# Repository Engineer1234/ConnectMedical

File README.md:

# Connect-Med-Hardware
Repository for Hardware files relating to Connect Medical

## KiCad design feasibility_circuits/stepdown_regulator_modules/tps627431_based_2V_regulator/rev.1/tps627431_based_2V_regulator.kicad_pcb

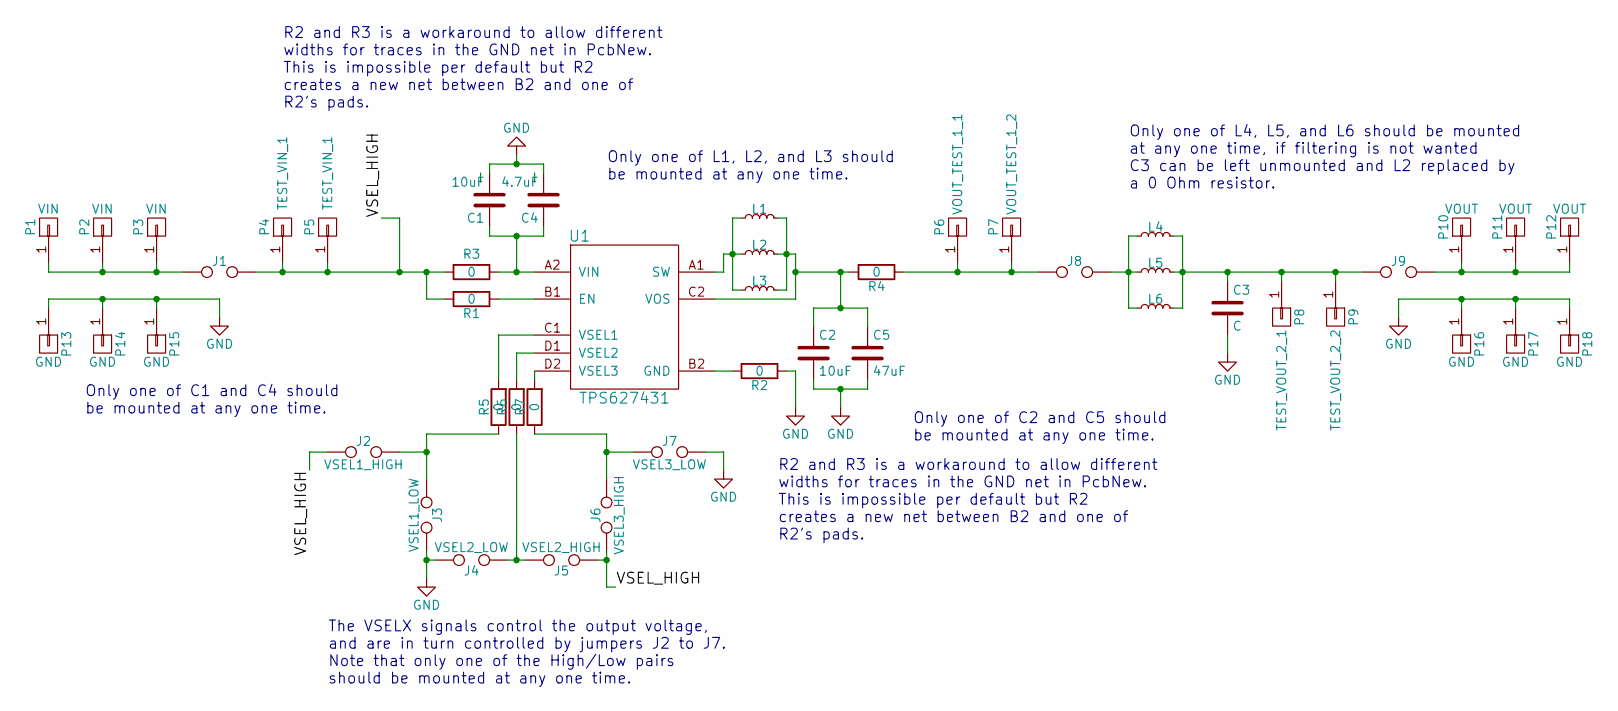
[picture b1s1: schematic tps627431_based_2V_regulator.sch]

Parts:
C1, C2: 10uF; C_0805_HandSoldering
C3: C; C_0805_HandSoldering
C4: 4.7uF; C_0402
C5: 47uF; C_0805_HandSoldering
J1, J8, J9: TEST; proto_header-vt-1x2-2.54mm-G_C__SABN_M30
J2: VSEL1_HIGH; proto_header-vt-1x2-2.54mm-G_C__SABN_M30
J3: VSEL1_LOW; proto_header-vt-1x2-2.54mm-G_C__SABN_M30
J4: VSEL2_LOW; proto_header-vt-1x2-2.54mm-G_C__SABN_M30
J5: VSEL2_HIGH; proto_header-vt-1x2-2.54mm-G_C__SABN_M30
J6: VSEL3_HIGH; proto_header-vt-1x2-2.54mm-G_C__SABN_M30
J7: VSEL3_LOW; proto_header-vt-1x2-2.54mm-G_C__SABN_M30
L1: L_Small; proto_inductor-WE_74404043100A_455x360
L2, L6: L_Small; proto_inductor-smd_1210
L3: L_Small; proto_inductor-WE_74404064220_640x570
L4: L_Small; proto_inductor-smd_1008
L5: L_Small; proto_inductor-smd_0805
P1, P2, P3: VIN; proto_pad-square-3mm
P4, P5: TEST_VIN_1; proto_pad-square-3mm
P6: VOUT_TEST_1_1; proto_pad-square-3mm
P7: VOUT_TEST_1_2; proto_pad-square-3mm
P8: TEST_VOUT_2_1; proto_pad-square-3mm
P9: TEST_VOUT_2_2; proto_pad-square-3mm
P10, P11, P12: VOUT; proto_pad-square-3mm
P13, P14, P15, P16, P17, P18: GND; proto_pad-square-3mm
R1, R2, R3, R4, R5, R6, R7: 0; R_0805_HandSoldering
U1: TPS627431; proto_amp-ti_tps624731

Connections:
/VSEL_HIGH: J1.2, J2.1, J5.1, J6.1, P4.1, P5.1, R1.2, R3.2
GND: C1.2, C2.2, C3.2, C4.2, C5.2, J3.2, J4.2, J7.2, P13.1, P14.1, P15.1, P16.1, P17.1, P18.1, R2.1
unnamed: C1.1, C4.1, R3.1, U1.A2 (VIN)
unnamed: C2.1, C5.1, L1.2, L2.2, L3.2, R4.2, U1.C2 (VOS)
unnamed: C3.1, J9.1, L4.2, L5.2, L6.2, P8.1, P9.1
unnamed: J1.1, P1.1, P2.1, P3.1
unnamed: J2.2, J3.1, R5.1
unnamed: J4.1, J5.2, R6.1
unnamed: J6.2, J7.1, R7.1
unnamed: J8.1, P6.1, P7.1, R4.1
unnamed: J8.2, L4.1, L5.1, L6.1
unnamed: J9.2, P10.1, P11.1, P12.1
unnamed: L1.1, L2.1, L3.1, U1.A1 (SW)
unnamed: R1.1, U1.B1 (EN)
unnamed: R2.2, U1.B2 (GND)
unnamed: R5.2, U1.C1 (VSEL1)
unnamed: R6.2, U1.D1 (VSEL2)
unnamed: R7.2, U1.D2 (VSEL3)

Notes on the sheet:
Only one of L4, L5, and L6 should be mounted at any one time, if filtering is not wanted C3 can be left unmounted and L2 replaced by a 0 Ohm resistor.
Only one of L1, L2, and L3 should be mounted at any one time.
The VSELX signals control the output voltage, and are in turn controlled by jumpers J2 to J7. Note that only one of the High/Low pairs should be mounted at any one time.
Only one of C1 and C4 should be mounted at any one time.
Only one of C2 and C5 should be mounted at any one time.
R2 and R3 is a workaround to allow different widths for traces in the GND net in PcbNew. This is impossible per default but R2 creates a new net between B2 and one of R2's pads.

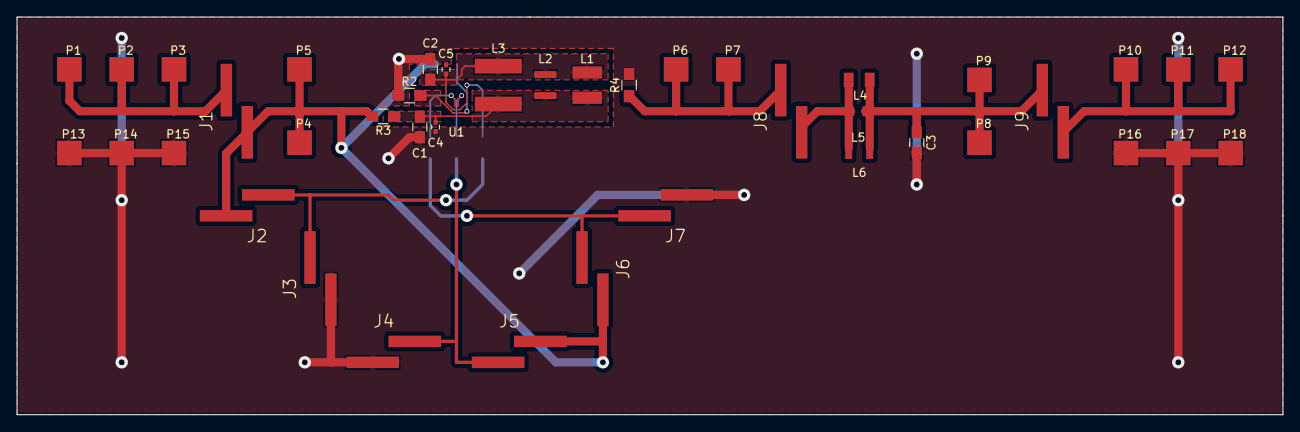
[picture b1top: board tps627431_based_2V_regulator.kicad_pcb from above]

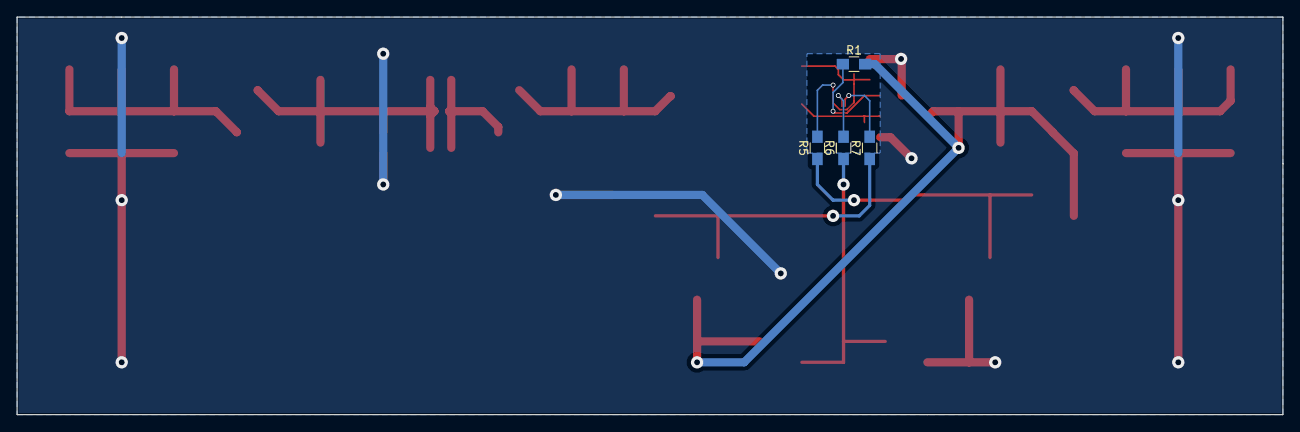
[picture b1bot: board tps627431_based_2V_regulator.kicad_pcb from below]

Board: 2 copper layers, 153.7 x 48.3 mm, 46 parts (4 on the bottom side), 18 nets.

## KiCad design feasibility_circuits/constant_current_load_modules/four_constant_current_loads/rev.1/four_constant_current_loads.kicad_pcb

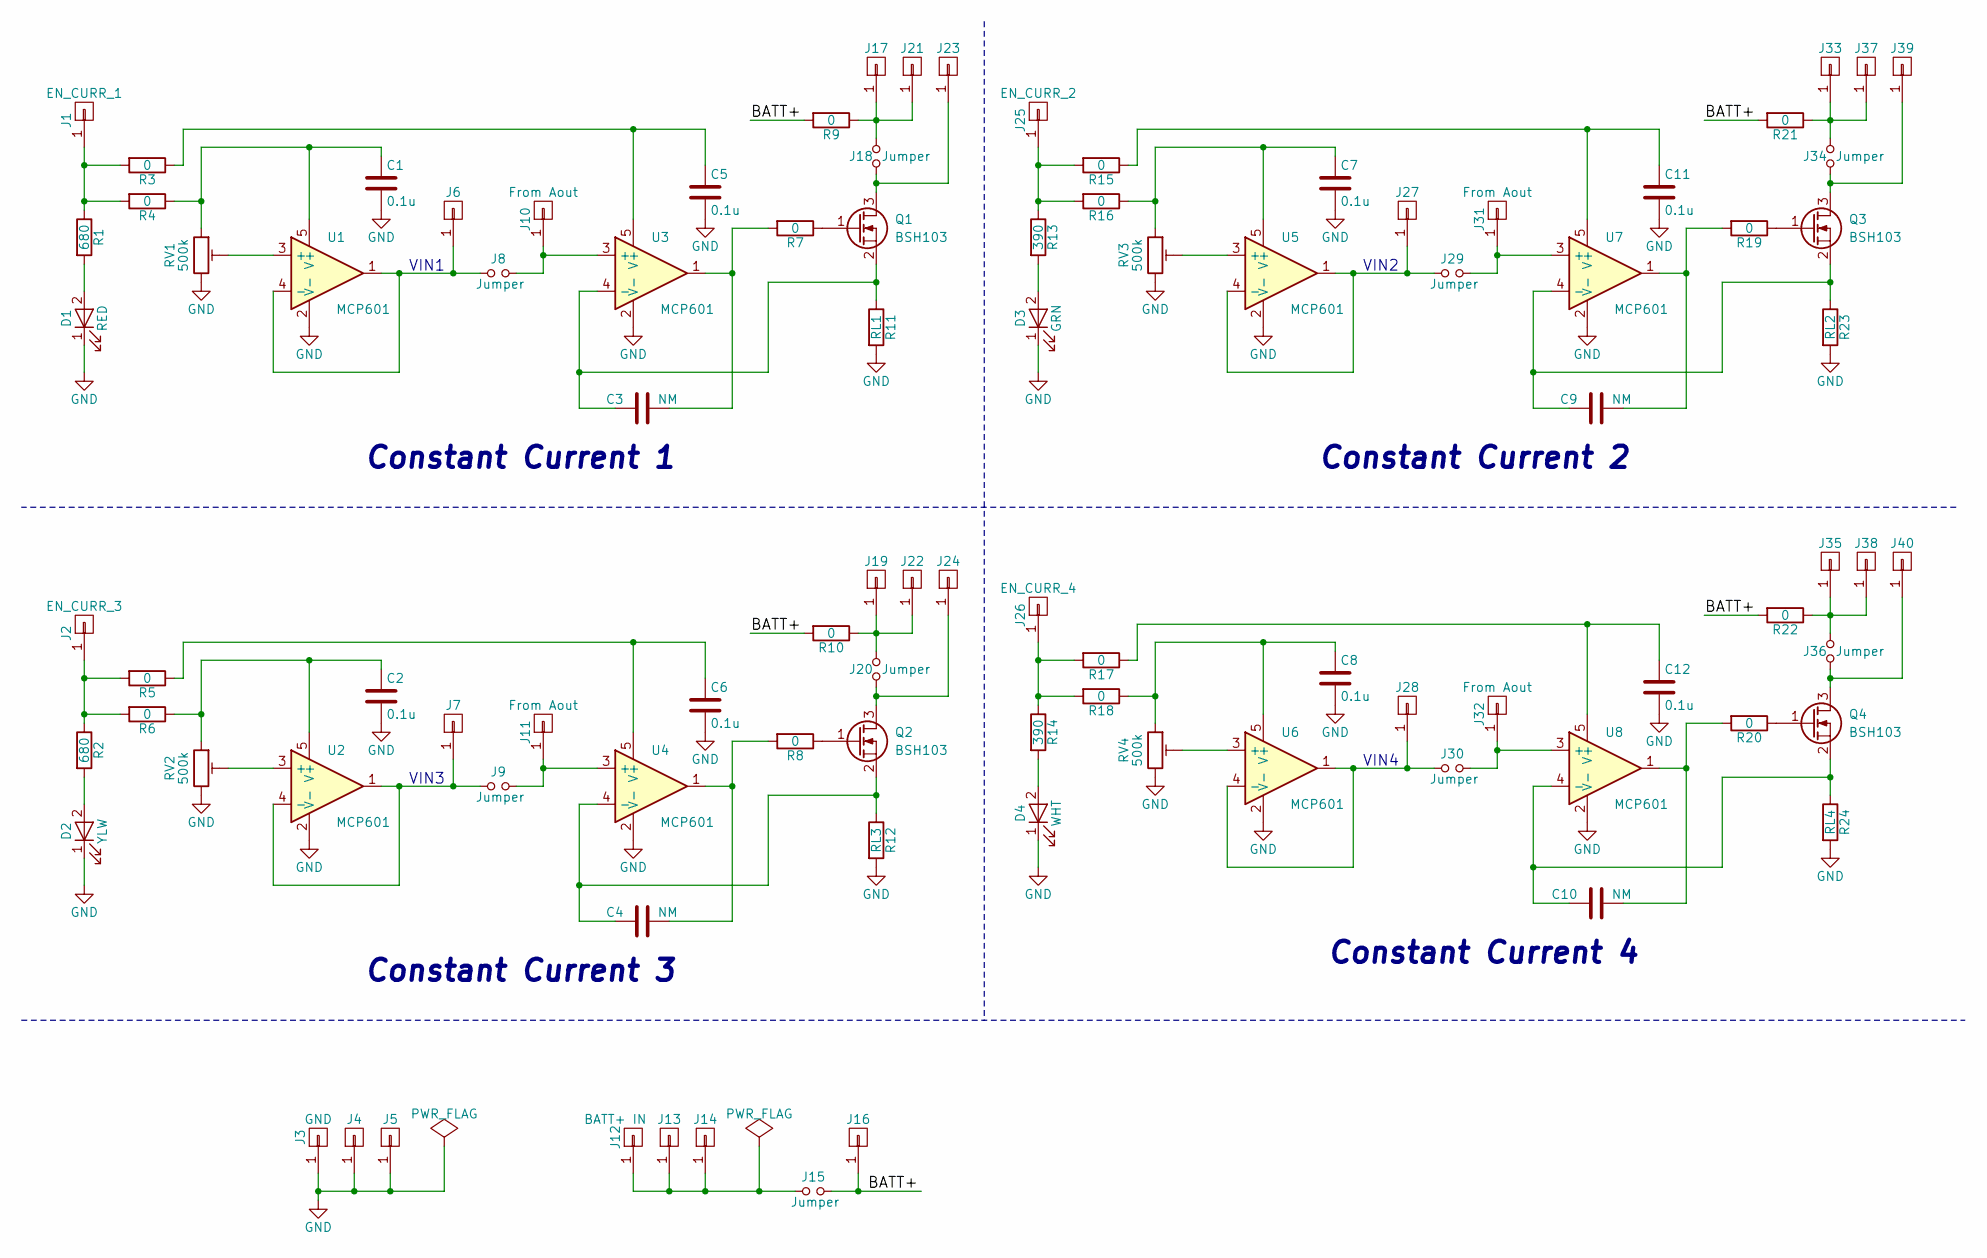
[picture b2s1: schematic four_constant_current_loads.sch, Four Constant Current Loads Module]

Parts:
C1, C2, C5, C6, C7, C8, C11, C12: 0.1u; C_0805_HandSoldering
C3, C4, C9, C10: NM; C_0805_HandSoldering
D1: RED; R_0805_HandSoldering
D2: YLW; R_0805_HandSoldering
D3: GRN; R_0805_HandSoldering
D4: WHT; R_0805_HandSoldering
J1: EN_CURR_1; proto_pad-square-3mm
J2: EN_CURR_3; proto_pad-square-3mm
J3, J4, J5, J6, J7, J13, J14, J16, J17, J19, J21, J22, J23, J24, J27, J28, J33, J35, J37, J38, J39, J40: GND; proto_pad-square-3mm
J8, J9, J15, J18, J20, J29, J30, J34, J36: Jumper; proto_header-vt-1x2-2.54mm-G_C__SABN_M30
J10, J11, J31, J32: From Aout; proto_pad-square-3mm
J12: BATT+ IN; proto_pad-square-3mm
J25: EN_CURR_2; proto_pad-square-3mm
J26: EN_CURR_4; proto_pad-square-3mm
Q1, Q2, Q3, Q4: BSH103; SOT-23_Handsoldering
R1, R2: 680; R_0805_HandSoldering
R3, R4, R5, R6, R7, R8, R9, R10, R15, R16, R17, R18, R19, R20, R21, R22: 0; R_0805_HandSoldering
R11: RL1; R_0805_HandSoldering
R12: RL3; R_0805_HandSoldering
R13, R14: 390; R_0805_HandSoldering
R23: RL2; R_0805_HandSoldering
R24: RL4; R_0805_HandSoldering
RV1, RV2, RV3, RV4: 500k; proto_pot-model_84w
U1, U2, U3, U4, U5, U6, U7, U8: MCP601; SOT-23-5_HandSoldering

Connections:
/BATT+: J15.2, J16.1, R9.2, R10.2, R21.2, R22.2
GND: C1.2, C2.2, C5.2, C6.2, C7.2, C8.2, C11.2, C12.2, D1.1 (K), D2.1 (K), D3.1 (K), D4.1 (K), J3.1, J4.1, J5.1, R11.2, R12.2, R23.2, R24.2, RV1.3, RV2.3, RV3.3, RV4.3, U1.2 (V-), U2.2 (V-), U3.2 (V-), U4.2 (V-), U5.2 (V-), U6.2 (V-), U7.2 (V-), U8.2 (V-)
unnamed: C1.1, R4.1, RV1.1, U1.5 (V+)
unnamed: C2.1, R6.1, RV2.1, U2.5 (V+)
unnamed: C3.1, Q1.2 (S), R11.1, U3.4 (-)
unnamed: C3.2, R7.2, U3.1
unnamed: C4.1, Q2.2 (S), R12.1, U4.4 (-)
unnamed: C4.2, R8.2, U4.1
unnamed: C5.1, R3.1, U3.5 (V+)
unnamed: C6.1, R5.1, U4.5 (V+)
unnamed: C7.1, R16.1, RV3.1, U5.5 (V+)
unnamed: C8.1, R18.1, RV4.1, U6.5 (V+)
unnamed: C9.1, Q3.2 (S), R23.1, U7.4 (-)
unnamed: C9.2, R19.2, U7.1
unnamed: C10.1, Q4.2 (S), R24.1, U8.4 (-)
unnamed: C10.2, R20.2, U8.1
unnamed: C11.1, R15.1, U7.5 (V+)
unnamed: C12.1, R17.1, U8.5 (V+)
unnamed: D1.2 (A), R1.2
unnamed: D2.2 (A), R2.2
unnamed: D3.2 (A), R13.2
unnamed: D4.2 (A), R14.2
unnamed: J1.1, R1.1, R3.2, R4.2
unnamed: J2.1, R2.1, R5.2, R6.2
unnamed: J6.1, J8.1, U1.1, U1.4 (-)
unnamed: J7.1, J9.1, U2.1, U2.4 (-)
unnamed: J8.2, J10.1, U3.3 (+)
unnamed: J9.2, J11.1, U4.3 (+)
unnamed: J12.1, J13.1, J14.1, J15.1
unnamed: J17.1, J18.1, J21.1, R9.1
unnamed: J18.2, J23.1, Q1.3 (D)
unnamed: J19.1, J20.1, J22.1, R10.1
unnamed: J20.2, J24.1, Q2.3 (D)
unnamed: J25.1, R13.1, R15.2, R16.2
unnamed: J26.1, R14.1, R17.2, R18.2
unnamed: J27.1, J29.1, U5.1, U5.4 (-)
unnamed: J28.1, J30.1, U6.1, U6.4 (-)
unnamed: J29.2, J31.1, U7.3 (+)
unnamed: J30.2, J32.1, U8.3 (+)
unnamed: J33.1, J34.1, J37.1, R21.1
unnamed: J34.2, J39.1, Q3.3 (D)
unnamed: J35.1, J36.1, J38.1, R22.1
unnamed: J36.2, J40.1, Q4.3 (D)
unnamed: Q1.1 (G), R7.1
unnamed: Q2.1 (G), R8.1
unnamed: Q3.1 (G), R19.1
unnamed: Q4.1 (G), R20.1
unnamed: RV1.2, U1.3 (+)
unnamed: RV2.2, U2.3 (+)
unnamed: RV3.2, U5.3 (+)
unnamed: RV4.2, U6.3 (+)

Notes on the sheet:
Constant Current 1
Constant Current 2
Constant Current 3
Constant Current 4
VIN1
VIN2
VIN3
VIN4

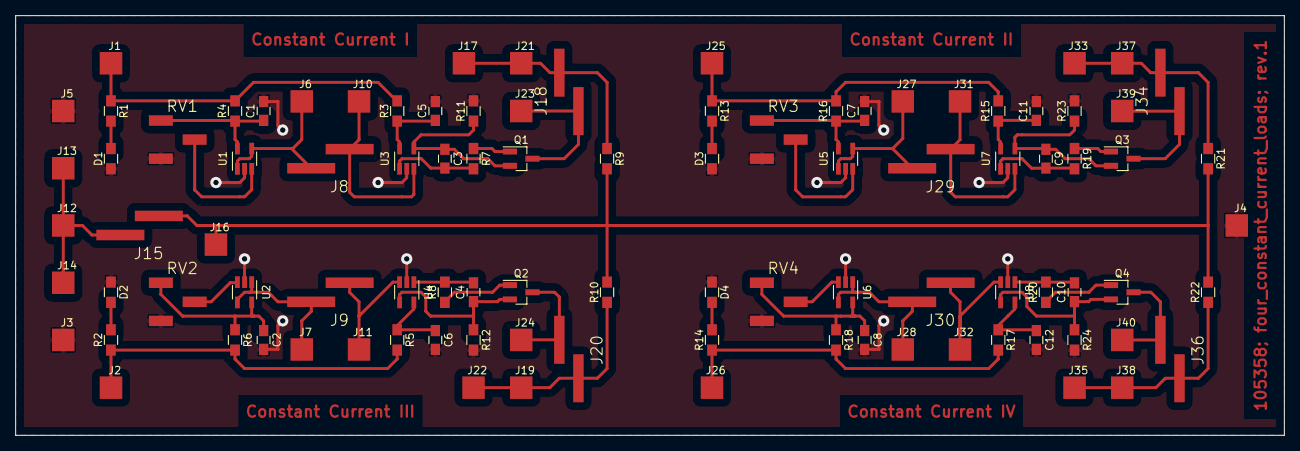
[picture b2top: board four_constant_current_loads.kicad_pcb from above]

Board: 2 copper layers, 168.9 x 55.9 mm, 96 parts (0 on the bottom side), 51 nets.

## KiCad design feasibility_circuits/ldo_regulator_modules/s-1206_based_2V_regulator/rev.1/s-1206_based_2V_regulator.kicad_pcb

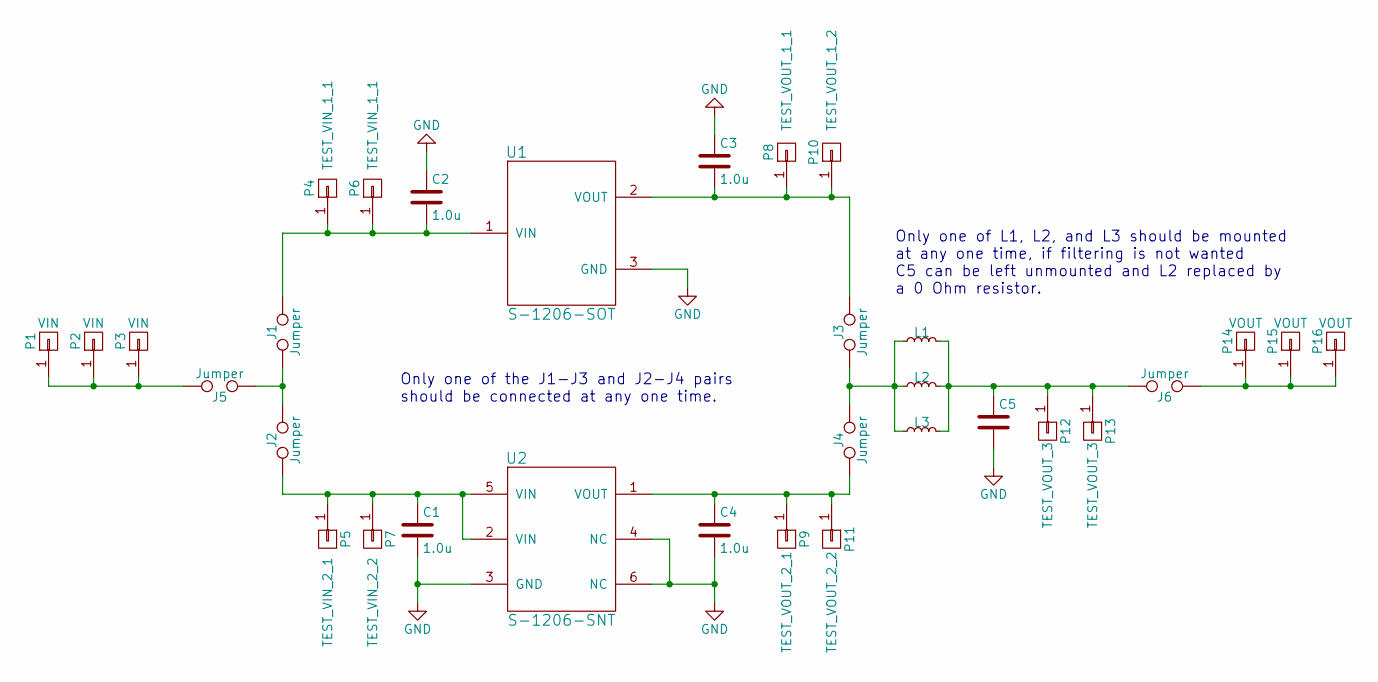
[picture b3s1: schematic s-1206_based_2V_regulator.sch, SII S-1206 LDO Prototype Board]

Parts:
C1, C2, C3, C4: 1.0u; C_0805_HandSoldering
C5: C; C_0805_HandSoldering
J1, J2, J3, J4, J5, J6: Jumper; proto_header-vt-1x2-2.54mm-G_C__SABN_M30
L1: L_Small; proto_inductor-smd_1210
L2: L_Small; proto_inductor-smd_0805
L3: L_Small; proto_inductor-smd_1008
P1, P2, P3: VIN; proto_pad-square-3mm
P4, P6: TEST_VIN_1_1; proto_pad-square-3mm
P5: TEST_VIN_2_1; proto_pad-square-3mm
P7: TEST_VIN_2_2; proto_pad-square-3mm
P8: TEST_VOUT_1_1; proto_pad-square-3mm
P9: TEST_VOUT_2_1; proto_pad-square-3mm
P10: TEST_VOUT_1_2; proto_pad-square-3mm
P11: TEST_VOUT_2_2; proto_pad-square-3mm
P12, P13: TEST_VOUT_3; proto_pad-square-3mm
P14, P15, P16: VOUT; proto_pad-square-3mm
U1: S-1206-SOT; proto_amp-sii_s_1206_SOT_23
U2: S-1206-SNT; proto_amp-sii_s_1206_SNT_6A

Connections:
GND: C1.2, C2.1, C3.1, C4.2, C5.2, U1.3 (GND), U2.3 (GND), U2.4 (NC), U2.6 (NC)
unnamed: C1.1, J2.1, P5.1, P7.1, U2.2 (VIN), U2.5 (VIN)
unnamed: C2.2, J1.2, P4.1, P6.1, U1.1 (VIN)
unnamed: C3.2, J3.2, P8.1, P10.1, U1.2 (VOUT)
unnamed: C4.1, J4.1, P9.1, P11.1, U2.1 (VOUT)
unnamed: C5.1, J6.2, L1.2, L2.2, L3.2, P12.1, P13.1
unnamed: J1.1, J2.2, J5.1
unnamed: J3.1, J4.2, L1.1, L2.1, L3.1
unnamed: J5.2, P1.1, P2.1, P3.1
unnamed: J6.1, P14.1, P15.1, P16.1

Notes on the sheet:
Only one of the J1-J3 and J2-J4 pairs should be connected at any one time.
Only one of L1, L2, and L3 should be mounted at any one time, if filtering is not wanted C5 can be left unmounted and L2 replaced by a 0 Ohm resistor.

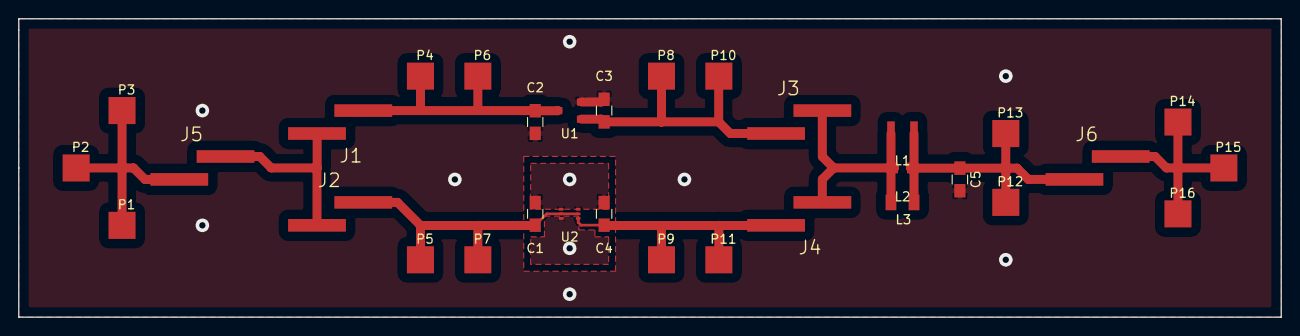
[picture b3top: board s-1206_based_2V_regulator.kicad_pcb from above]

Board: 2 copper layers, 139.7 x 33.0 mm, 32 parts (0 on the bottom side), 10 nets.

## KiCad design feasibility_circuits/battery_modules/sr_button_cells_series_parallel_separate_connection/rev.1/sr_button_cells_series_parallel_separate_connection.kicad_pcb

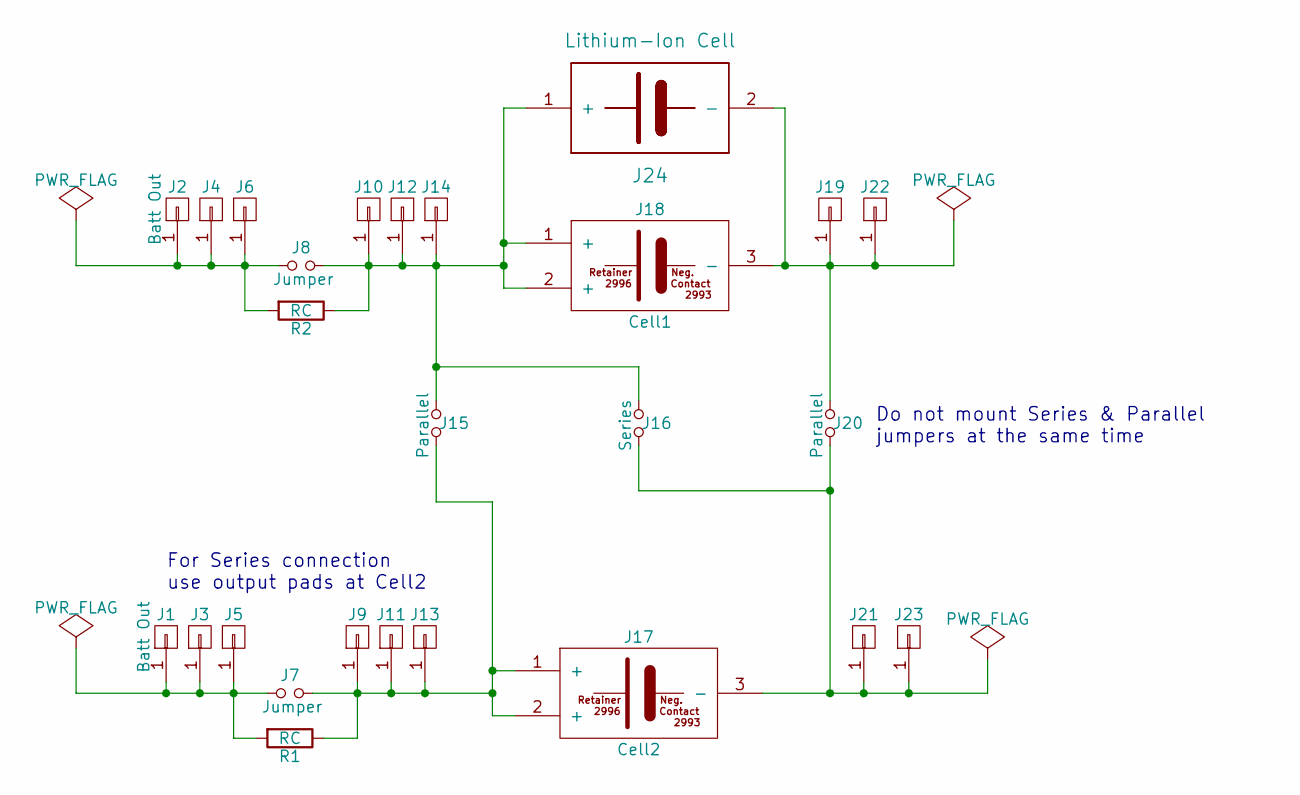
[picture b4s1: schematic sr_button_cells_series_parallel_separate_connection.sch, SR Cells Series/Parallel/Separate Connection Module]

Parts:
J1, J2: Batt Out; proto_pad-square-3mm
J3, J4, J5, J6, J9, J10, J11, J12, J13, J14, J19, J21, J22, J23: CONN_01X01; proto_pad-square-3mm
J7, J8: Jumper; proto_header-vt-1x2-2.54mm-G_C__SABN_M30
J15, J20: Parallel; proto_header-vt-1x2-2.54mm-G_C__SABN_M30
J16: Series; proto_header-vt-1x2-2.54mm-G_C__SABN_M30
J17: Cell2; proto_button_cell_holder-smd-2996-2993
J18: Cell1; proto_button_cell_holder-smd-2996-2993
J24: Lithium-Ion Cell; proto_button_cell_holder-smd-498
R1, R2: RC; R_0805_HandSoldering

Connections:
unnamed: J1.1, J3.1, J5.1, J7.1, R1.2
unnamed: J2.1, J4.1, J6.1, J8.1, R2.2
unnamed: J8.2, J10.1, J12.1, J14.1, J15.1, J16.1, J18.1 (+), J18.2 (+), J24.1 (+), R2.1
unnamed: J7.2, J9.1, J11.1, J13.1, J15.2, J17.1 (+), J17.2 (+), R1.1
unnamed: J16.2, J17.3 (-), J20.2, J21.1, J23.1
unnamed: J18.3 (-), J19.1, J20.1, J22.1, J24.2 (-)

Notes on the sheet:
Do not mount Series & Parallel jumpers at the same time
For Series connection use output pads at Cell2

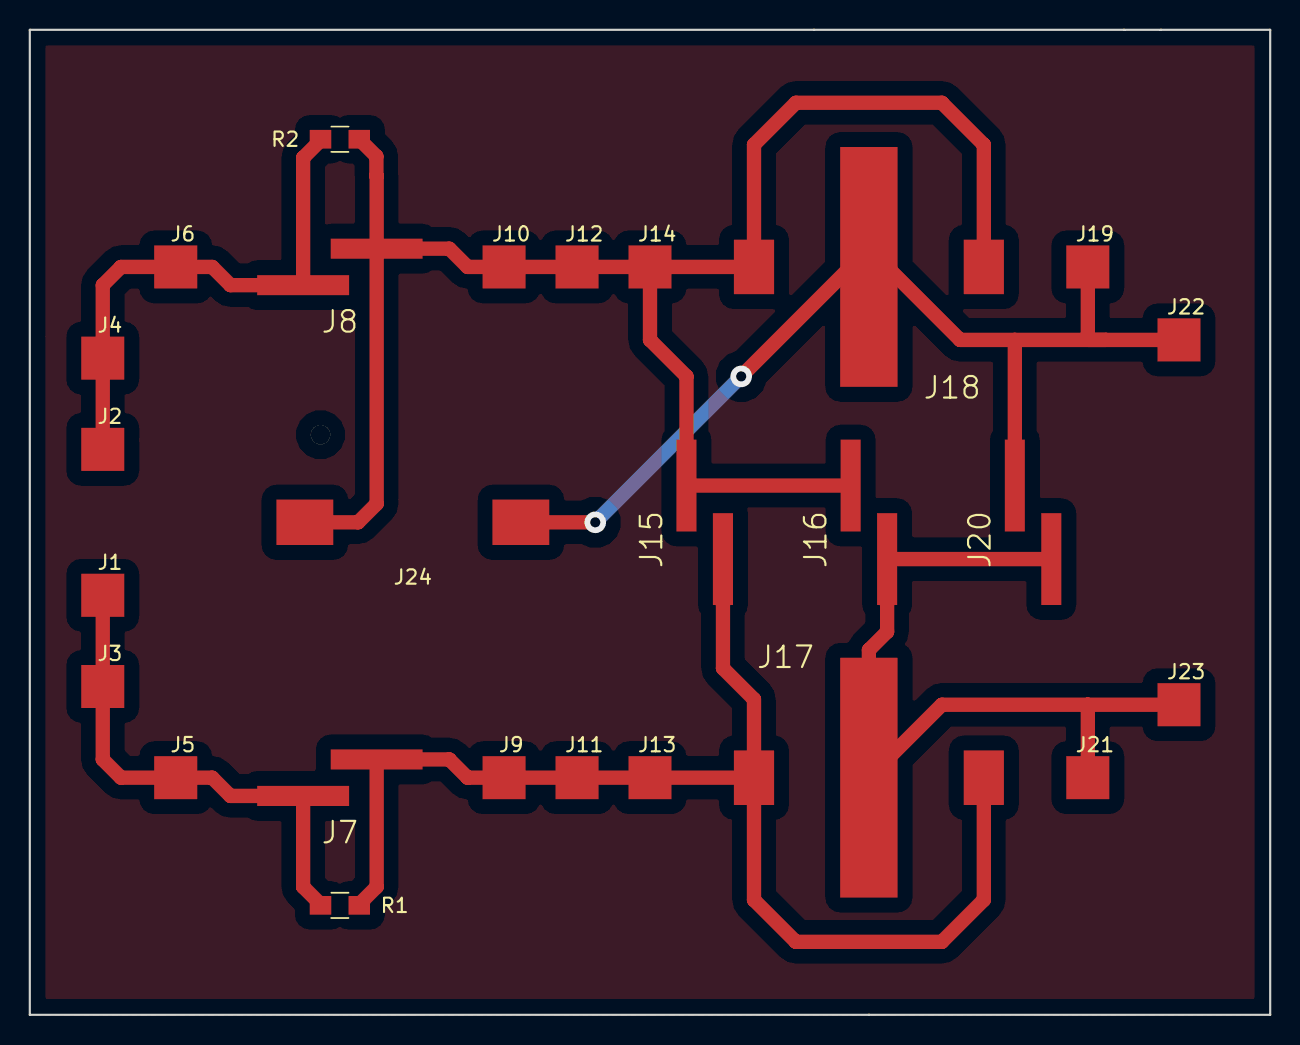
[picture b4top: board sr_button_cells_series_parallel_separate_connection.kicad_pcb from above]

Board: 2 copper layers, 86.4 x 68.6 mm, 26 parts (0 on the bottom side), 6 nets.

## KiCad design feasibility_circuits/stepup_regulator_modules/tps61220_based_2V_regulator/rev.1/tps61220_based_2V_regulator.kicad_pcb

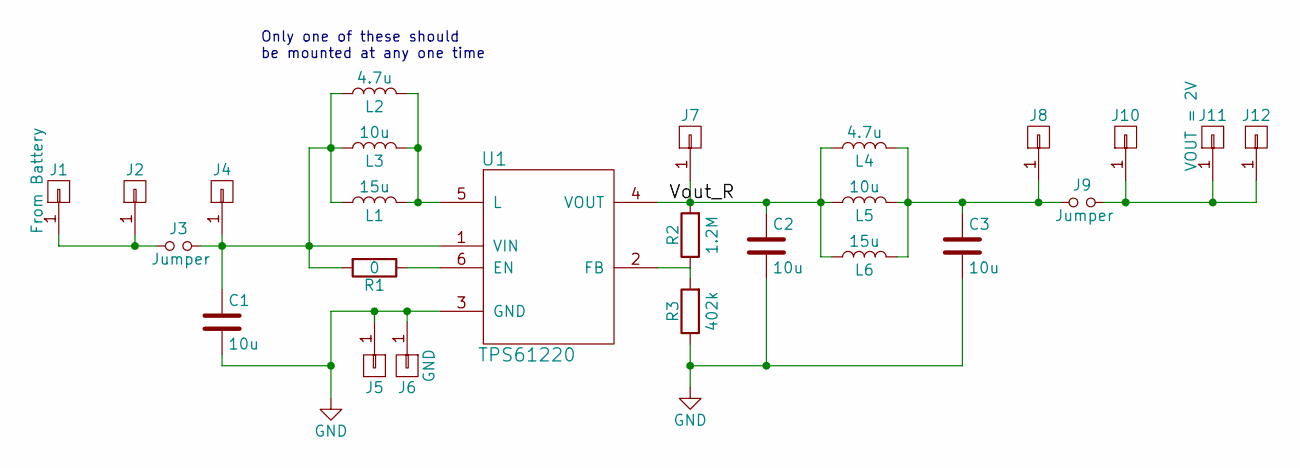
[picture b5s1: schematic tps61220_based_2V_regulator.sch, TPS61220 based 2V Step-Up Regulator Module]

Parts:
C1, C2, C3: 10u; C_0805_HandSoldering
J1, J2, J4, J5, J7, J8, J10, J12: From Battery; proto_pad-square-3mm
J3, J9: Jumper; proto_header-vt-1x2-2.54mm-G_C__SABN_M30
J6: GND; proto_pad-square-3mm
J11: VOUT = 2V; proto_pad-square-3mm
L1, L6: 15u; proto_inductor-smd_1210
L2, L4: 4.7u; proto_inductor-smd_0805
L3, L5: 10u; proto_inductor-smd_1008
R1: 0; R_0805_HandSoldering
R2: 1.2M; R_0805_HandSoldering
R3: 402k; R_0805_HandSoldering
U1: TPS61220; proto_amp-ti_tps6122

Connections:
/Vout_R: C2.1, J7.1, L4.1, L5.1, L6.1, R2.2, U1.4 (VOUT)
GND: C1.2, C2.2, C3.2, J5.1, J6.1, R3.1, U1.3 (GND)
unnamed: C1.1, J3.2, J4.1, L1.1, L2.1, L3.1, R1.2, U1.1 (VIN)
unnamed: C3.1, J8.1, J9.1, L4.2, L5.2, L6.2
unnamed: J1.1, J2.1, J3.1
unnamed: J9.2, J10.1, J11.1, J12.1
unnamed: L1.2, L2.2, L3.2, U1.5 (L)
unnamed: R1.1, U1.6 (EN)
unnamed: R2.1, R3.2, U1.2 (FB)

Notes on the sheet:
Only one of these should be mounted at any one time

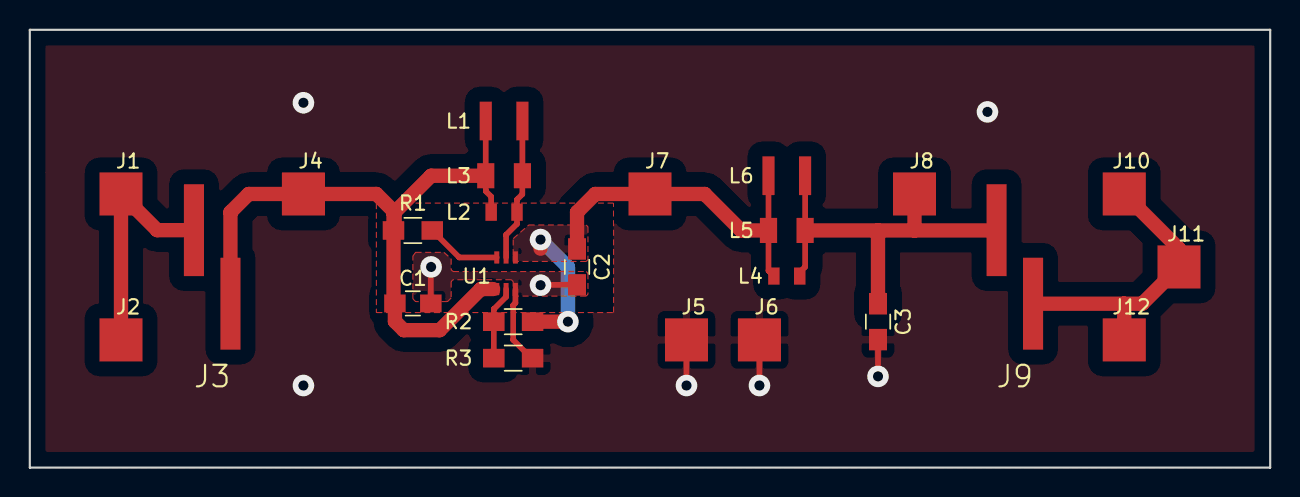
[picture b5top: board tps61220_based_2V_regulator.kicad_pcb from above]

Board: 2 copper layers, 86.4 x 30.5 mm, 25 parts (0 on the bottom side), 9 nets.

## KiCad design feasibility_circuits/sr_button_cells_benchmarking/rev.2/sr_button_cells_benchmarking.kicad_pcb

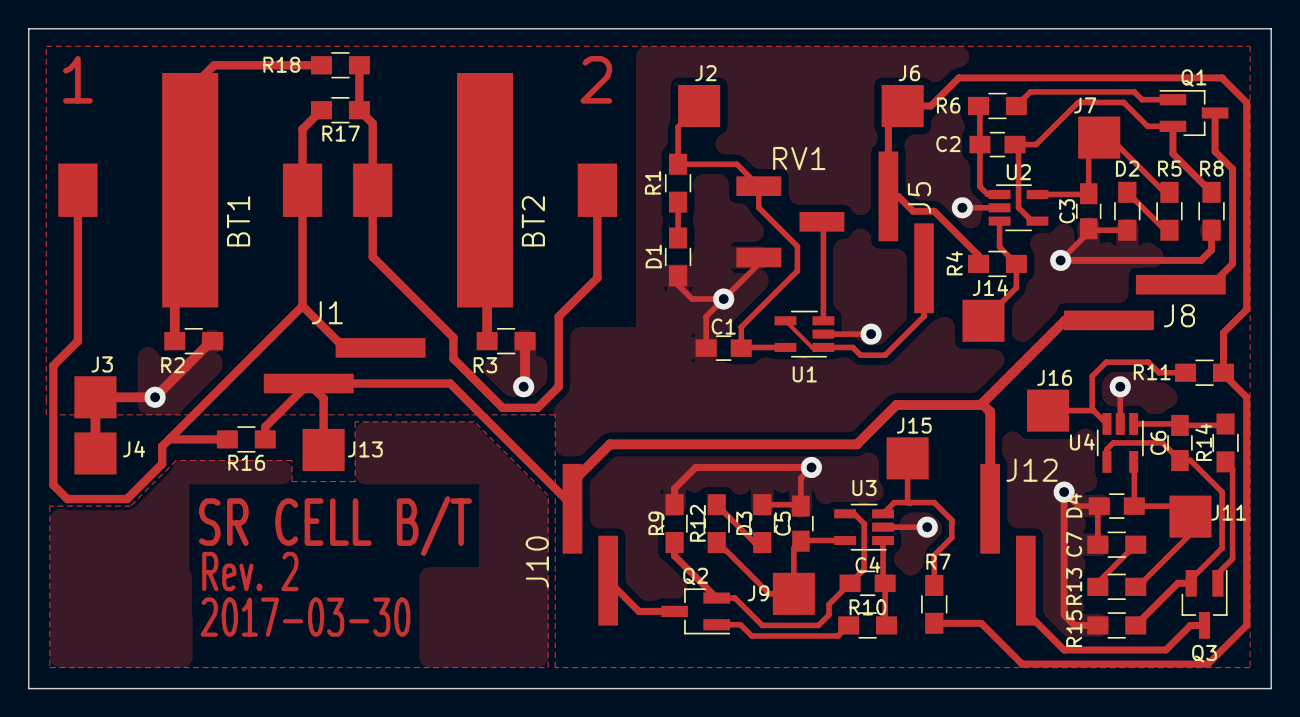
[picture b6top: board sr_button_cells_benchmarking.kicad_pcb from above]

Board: 2 copper layers, 88.5 x 47.0 mm, 55 parts (0 on the bottom side), 32 nets.

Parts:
BT1: Cell1; proto_sm_coin_cell_holder-2996-2993
BT2: Cell2; proto_sm_coin_cell_holder-2996-2993
C1, C3, C5, C7: 0.1u; C_0805_HandSoldering
C2, C4, C6: C; C_0805_HandSoldering
D1: RED; R_0805_HandSoldering
D2: WHT; R_0805_HandSoldering
D3: GRN; R_0805_HandSoldering
D4: YLW; R_0805_HandSoldering
J1: Current Measurement; proto_smd_header-1x2-2.54mm-G_C__SABN_M30
J2: EN_POT; proto_smd_pad-sq.-3mm
J3, J4: GND; proto_smd_pad-sq.-3mm
J5, J8, J10, J12: Jumper; proto_smd_header-1x2-2.54mm-G_C__SABN_M30
J6: VIN; proto_smd_pad-sq.-3mm
J7: EN_HIGH_CURR; proto_smd_pad-sq.-3mm
J9: EN_LOW_CURR; proto_smd_pad-sq.-3mm
J11: EN_MED_CURR; proto_smd_pad-sq.-3mm
J13: BATT+; proto_smd_pad-sq.-3mm
J14, J15, J16: Aout; proto_pad-square-3mm
Q1, Q2, Q3: BSH103; SOT-23_Handsoldering
R1, R13: 680; R_0805_HandSoldering
R2, R3, R4, R6, R7, R10, R11, R14, R17, R18: 0; R_0805_HandSoldering
R5, R9: 390; R_0805_HandSoldering
R8: RLH; R_0805_HandSoldering
R12: RLL; R_0805_HandSoldering
R15: RLM; R_0805_HandSoldering
R16: RC; R_0805_HandSoldering
RV1: 500k; proto_smd_pot-model_84w
U1, U2, U3, U4: MCP601; SOT-23-5_HandSoldering

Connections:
/BATT+: J1.2, J8.1, J10.1, J12.1, J13.1, R16.1
/VIN: J5.2, J6.1, R4.2, R7.2, R11.2
GND: C1.2, C3.2, C5.2, C7.2, D1.1, D2.1, D3.1, D4.1, J3.1, J4.1, R2.2, R3.2, R8.1, R12.1, R15.1, RV1.3, U1.2, U2.2, U3.2, U4.2
unnamed: BT1.1, BT1.2, J1.1, R16.2, R17.2
unnamed: BT1.3, R2.1, R18.2
unnamed: BT2.1, BT2.2, R17.1, R18.1
unnamed: BT2.3, R3.1
unnamed: C1.1, J2.1, R1.1, RV1.1, U1.5
unnamed: C2.1, Q1.2, R8.2, U2.4
unnamed: C2.2, R6.2, U2.1
unnamed: C3.1, J7.1, R5.1, U2.5
unnamed: C4.1, Q2.2, R12.2, U3.4
unnamed: C4.2, R10.2, U3.1
unnamed: C5.1, J9.1, R9.1, U3.5
unnamed: C6.1, Q3.2, R15.2, U4.4
unnamed: C6.2, R14.2, U4.1
unnamed: C7.1, J11.1, R13.1, U4.5
unnamed: D1.2, R1.2
unnamed: D2.2, R5.2
unnamed: D3.2, R9.2
unnamed: D4.2, R13.2
unnamed: J5.1, U1.1, U1.4
unnamed: J8.2, Q1.3
unnamed: J10.2, Q2.3
unnamed: J12.2, Q3.3
unnamed: J14.1, R4.1, U2.3
unnamed: J15.1, R7.1, U3.3
unnamed: J16.1, R11.1, U4.3
unnamed: Q1.1, R6.1
unnamed: Q2.1, R10.1
unnamed: Q3.1, R14.1
unnamed: RV1.2, U1.3

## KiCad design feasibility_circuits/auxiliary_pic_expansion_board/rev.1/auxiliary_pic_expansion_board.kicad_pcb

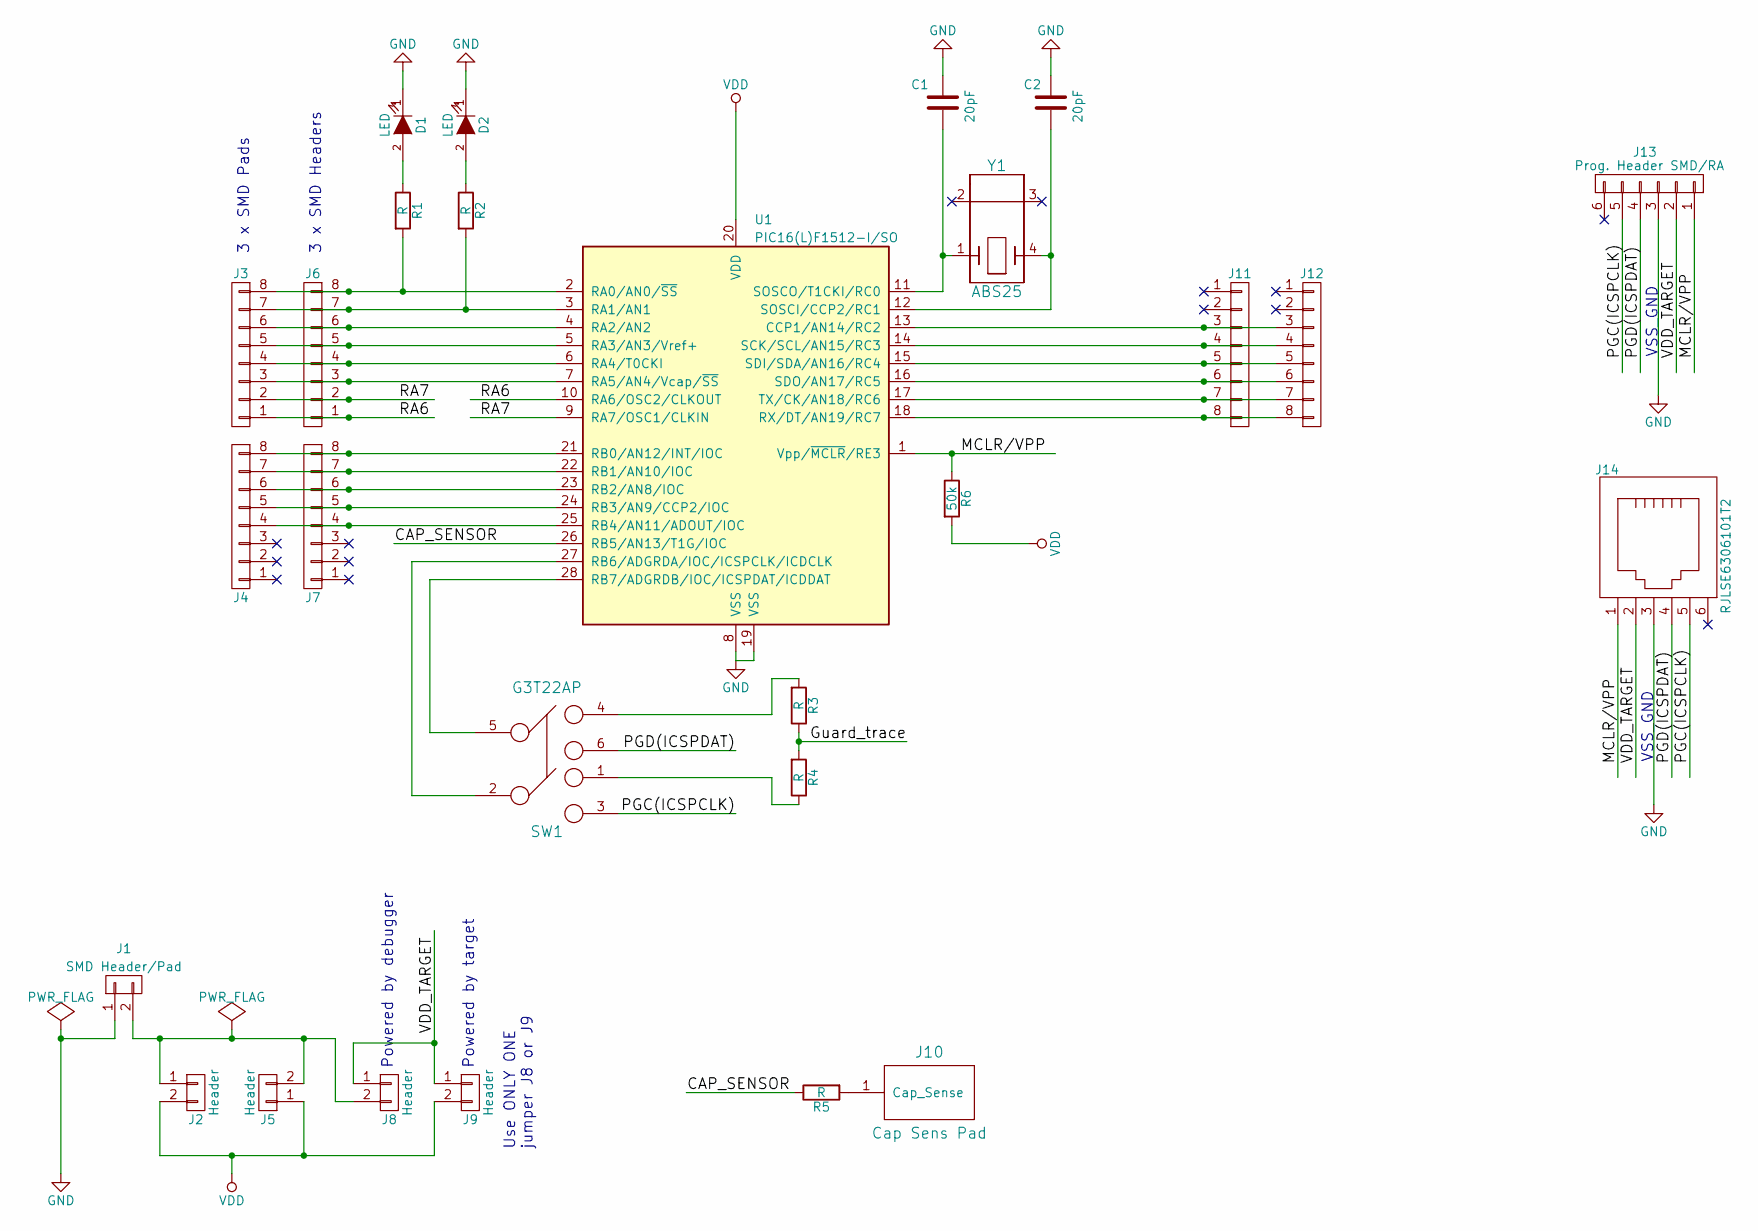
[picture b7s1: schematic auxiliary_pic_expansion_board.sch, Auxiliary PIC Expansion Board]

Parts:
C1, C2: 20pF; C_0805_HandSoldering
D1, D2: LED; R_0805_HandSoldering
J1: SMD Header/Pad; proto_header-vt-1x2-2.54mm-G_C__SABN_M30
J2, J5, J8, J9: Header; proto_header-vt-1x2-2.54mm-G_C__SABN_M30
J3, J4, J12: CONN_01X08; wire_solder_pad_2.54mm_1x8
J6, J7, J11: CONN_01X08; Sullins_SMD_pin_header_1x8_GBC36SABN-M30
J10: Cap Sens Pad; Capsense_Pad
J13: Prog. Header SMD/RA; proto_header-hz-1x6-2.54mm-G_C__SABN_M89
J14: RJLSE6306101T2; RJ11_SMD_Socket
R1, R2, R3, R4, R5: R; R_0805_HandSoldering
R6: 50k; R_0805_HandSoldering
SW1: G3T22AP; NKKSwitches_G3T22AP
U1: PIC16(L)F1512-I/SO; SOIC-28W_7.5x17.9mm_Pitch1.27mm
Y1: ABS25; Abracon_ABS25

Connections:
/CAP_SENSOR: R5.1, U1.26 (RB5/AN13/T1G/IOC)
/Guard_trace: R3.1, R4.2
/MCLR/VPP: J13.1, J14.1, R6.1, U1.1 (Vpp/~MCLR~/RE3)
/PGC(ICSPCLK): J13.5, J14.5, SW1.3
/PGD(ICSPDAT): J13.4, J14.4, SW1.6
/RA6: J3.1, J6.1, U1.10 (RA6/OSC2/CLKOUT)
/RA7: J3.2, J6.2, U1.9 (RA7/OSC1/CLKIN)
/VDD_TARGET: J8.1, J9.1, J13.2, J14.2
GND: C1.2, C2.2, D1.1 (K), D2.1 (K), J1.1, J13.3, J14.3, U1.8 (VSS), U1.19 (VSS)
unnamed: C1.1, U1.11 (SOSCO/T1CKI/RC0), Y1.1
unnamed: C2.1, U1.12 (SOSCI/CCP2/RC1), Y1.4
unnamed: D1.2 (A), R1.1
unnamed: D2.2 (A), R2.1
unnamed: J1.2, J2.1, J5.2, J8.2
unnamed: J3.3, J6.3, U1.7 (RA5/AN4/Vcap/~SS)
unnamed: J3.4, J6.4, U1.6 (RA4/T0CKI)
unnamed: J3.5, J6.5, U1.5 (RA3/AN3/Vref+)
unnamed: J3.6, J6.6, U1.4 (RA2/AN2)
unnamed: J3.7, J6.7, R2.2, U1.3 (RA1/AN1)
unnamed: J3.8, J6.8, R1.2, U1.2 (RA0/AN0/~SS)
unnamed: J4.4, J7.4, U1.25 (RB4/AN11/ADOUT/IOC)
unnamed: J4.5, J7.5, U1.24 (RB3/AN9/CCP2/IOC)
unnamed: J4.6, J7.6, U1.23 (RB2/AN8/IOC)
unnamed: J4.7, J7.7, U1.22 (RB1/AN10/IOC)
unnamed: J4.8, J7.8, U1.21 (RB0/AN12/INT/IOC)
unnamed: J10.1, R5.2
unnamed: J11.3, J12.3, U1.13 (CCP1/AN14/RC2)
unnamed: J11.4, J12.4, U1.14 (SCK/SCL/AN15/RC3)
unnamed: J11.5, J12.5, U1.15 (SDI/SDA/AN16/RC4)
unnamed: J11.6, J12.6, U1.16 (SDO/AN17/RC5)
unnamed: J11.7, J12.7, U1.17 (TX/CK/AN18/RC6)
unnamed: J11.8, J12.8, U1.18 (RX/DT/AN19/RC7)
unnamed: R3.2, SW1.4
unnamed: R4.1, SW1.1
unnamed: SW1.2, U1.27 (RB6/ADGRDA/IOC/ICSPCLK/ICDCLK)
unnamed: SW1.5, U1.28 (RB7/ADGRDB/IOC/ICSPDAT/ICDDAT)
VDD: J2.2, J5.1, J9.2, R6.2, U1.20 (VDD)

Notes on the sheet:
3 x SMD Headers
3 x SMD Pads
Powered by target
Powered by debugger
Use ONLY ONE jumper J8 or J9
VSS_GND
